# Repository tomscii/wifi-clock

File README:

NTP-sync'd clock with Raspberry Pico W
including SNMP agent serving temperature/humidity sensor values

See: https://tomscii.sig7.se/wifi-clock

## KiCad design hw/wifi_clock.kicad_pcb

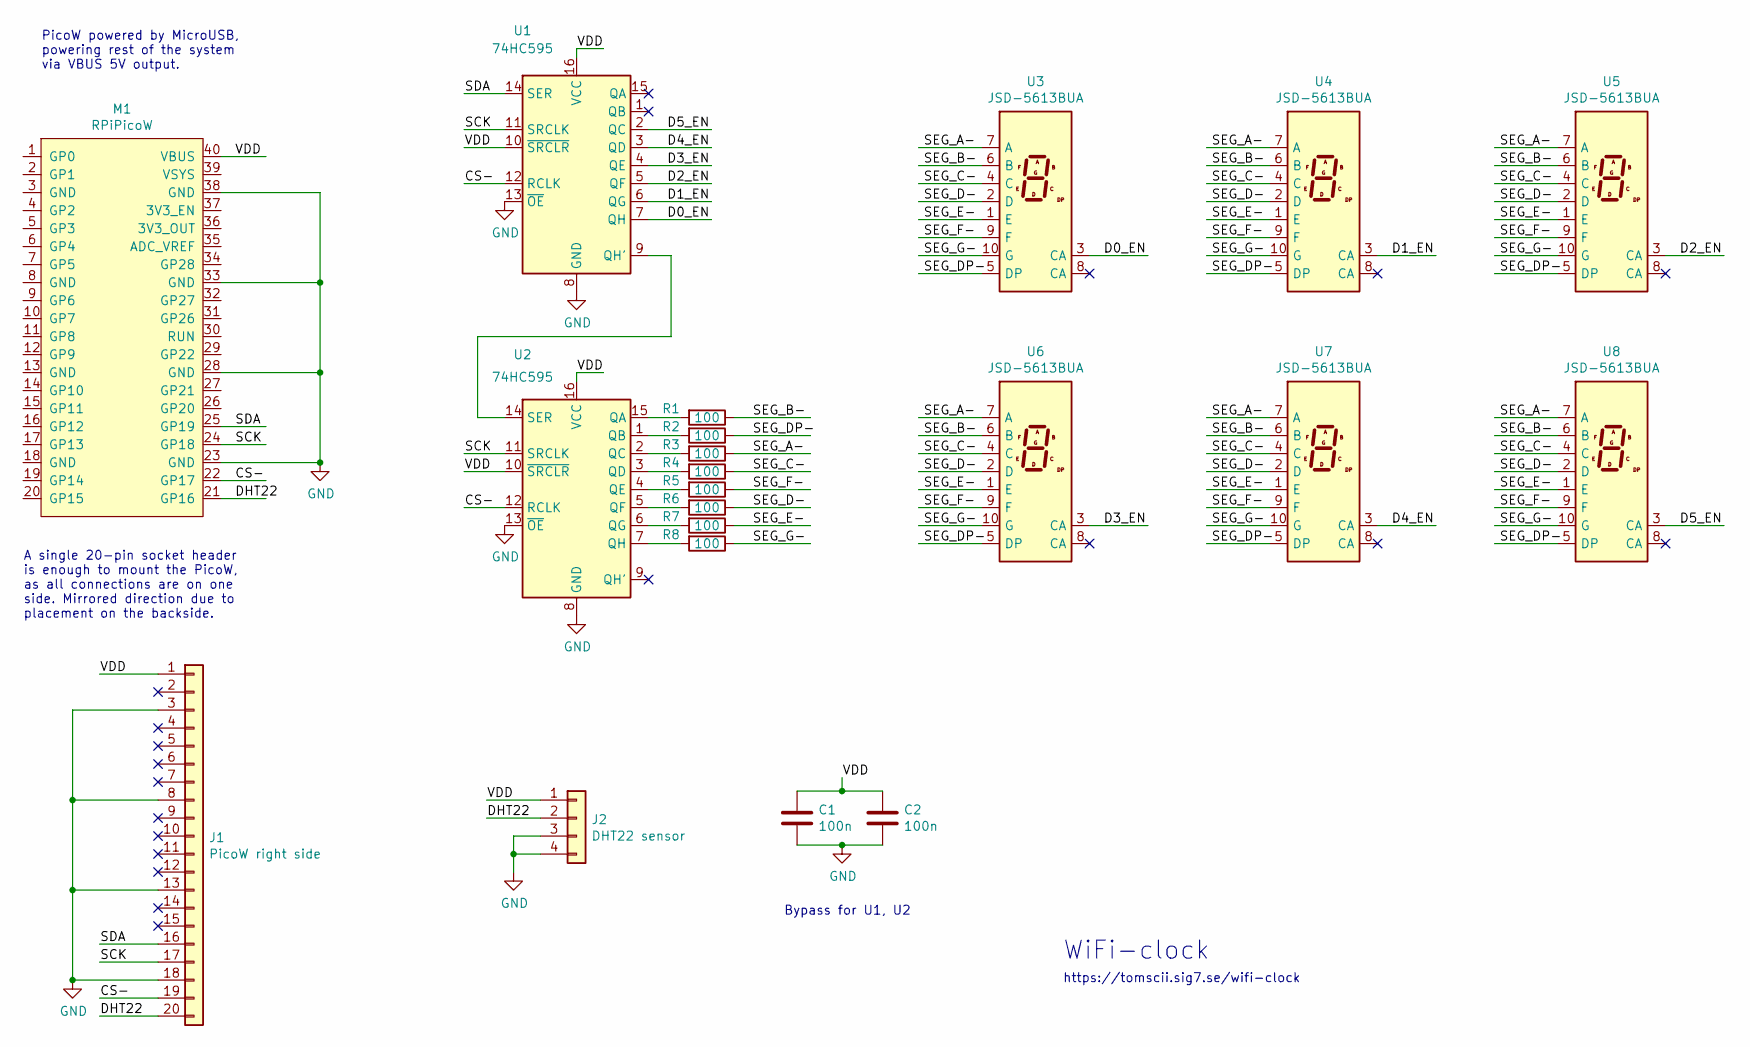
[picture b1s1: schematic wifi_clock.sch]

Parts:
C1, C2: 100n; C_Rect_L7.2mm_W2.5mm_P5.00mm_FKS2_FKP2_MKS2_MKP2
J1: PicoW right side; PinSocket_1x20_P2.54mm_Vertical
J2: DHT22 sensor; PinSocket_1x04_P2.54mm_Vertical
M1: RPiPicoW
R1, R2, R3, R4, R5, R6, R7, R8: 100; R_Axial_DIN0204_L3.6mm_D1.6mm_P7.62mm_Horizontal
U1, U2: 74HC595; DIP-16_W7.62mm
U3, U4, U5, U6, U7, U8: JSD-5613BUA; 7SegmentLED_LTS6760_LTS6780

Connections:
/CS-: J1.19, M1.22 (GP17), U1.12 (RCLK), U2.12 (RCLK)
/D0_EN: U1.7 (QH), U3.3 (CA)
/D1_EN: U1.6 (QG), U4.3 (CA)
/D2_EN: U1.5 (QF), U5.3 (CA)
/D3_EN: U1.4 (QE), U6.3 (CA)
/D4_EN: U1.3 (QD), U7.3 (CA)
/D5_EN: U1.2 (QC), U8.3 (CA)
/DHT22: J1.20, J2.2, M1.21 (GP16)
/SCK: J1.17, M1.24 (GP18), U1.11 (SRCLK), U2.11 (SRCLK)
/SDA: J1.16, M1.25 (GP19), U1.14 (SER)
/SEG_A-: R3.1, U3.7 (A), U4.7 (A), U5.7 (A), U6.7 (A), U7.7 (A), U8.7 (A)
/SEG_B-: R1.1, U3.6 (B), U4.6 (B), U5.6 (B), U6.6 (B), U7.6 (B), U8.6 (B)
/SEG_C-: R4.1, U3.4 (C), U4.4 (C), U5.4 (C), U6.4 (C), U7.4 (C), U8.4 (C)
/SEG_D-: R6.1, U3.2 (D), U4.2 (D), U5.2 (D), U6.2 (D), U7.2 (D), U8.2 (D)
/SEG_DP-: R2.1, U3.5 (DP), U4.5 (DP), U5.5 (DP), U6.5 (DP), U7.5 (DP), U8.5 (DP)
/SEG_E-: R7.1, U3.1 (E), U4.1 (E), U5.1 (E), U6.1 (E), U7.1 (E), U8.1 (E)
/SEG_F-: R5.1, U3.9 (F), U4.9 (F), U5.9 (F), U6.9 (F), U7.9 (F), U8.9 (F)
/SEG_G-: R8.1, U3.10 (G), U4.10 (G), U5.10 (G), U6.10 (G), U7.10 (G), U8.10 (G)
/VDD: C1.1, C2.1, J1.1, J2.1, M1.40 (VBUS), U1.10 (~SRCLR), U1.16 (VCC), U2.10 (~SRCLR), U2.16 (VCC)
GND: C1.2, C2.2, J1.3, J1.8, J1.13, J1.18, J2.3, J2.4, M1.23 (GND), M1.28 (GND), M1.33 (GND), M1.38 (GND), U1.8 (GND), U1.13 (~OE), U2.8 (GND), U2.13 (~OE)
unnamed: R1.2, U2.15 (QA)
unnamed: R2.2, U2.1 (QB)
unnamed: R3.2, U2.2 (QC)
unnamed: R4.2, U2.3 (QD)
unnamed: R5.2, U2.4 (QE)
unnamed: R6.2, U2.5 (QF)
unnamed: R7.2, U2.6 (QG)
unnamed: R8.2, U2.7 (QH)
unnamed: U1.9 (QH'), U2.14 (SER)

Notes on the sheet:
PicoW powered by MicroUSB, powering rest of the system via VBUS 5V output.
A single 20-pin socket header is enough to mount the PicoW, as all connections are on one side. Mirrored direction due to placement on the backside.
WiFi-clock
https://tomscii.sig7.se/wifi-clock
Bypass for U1, U2

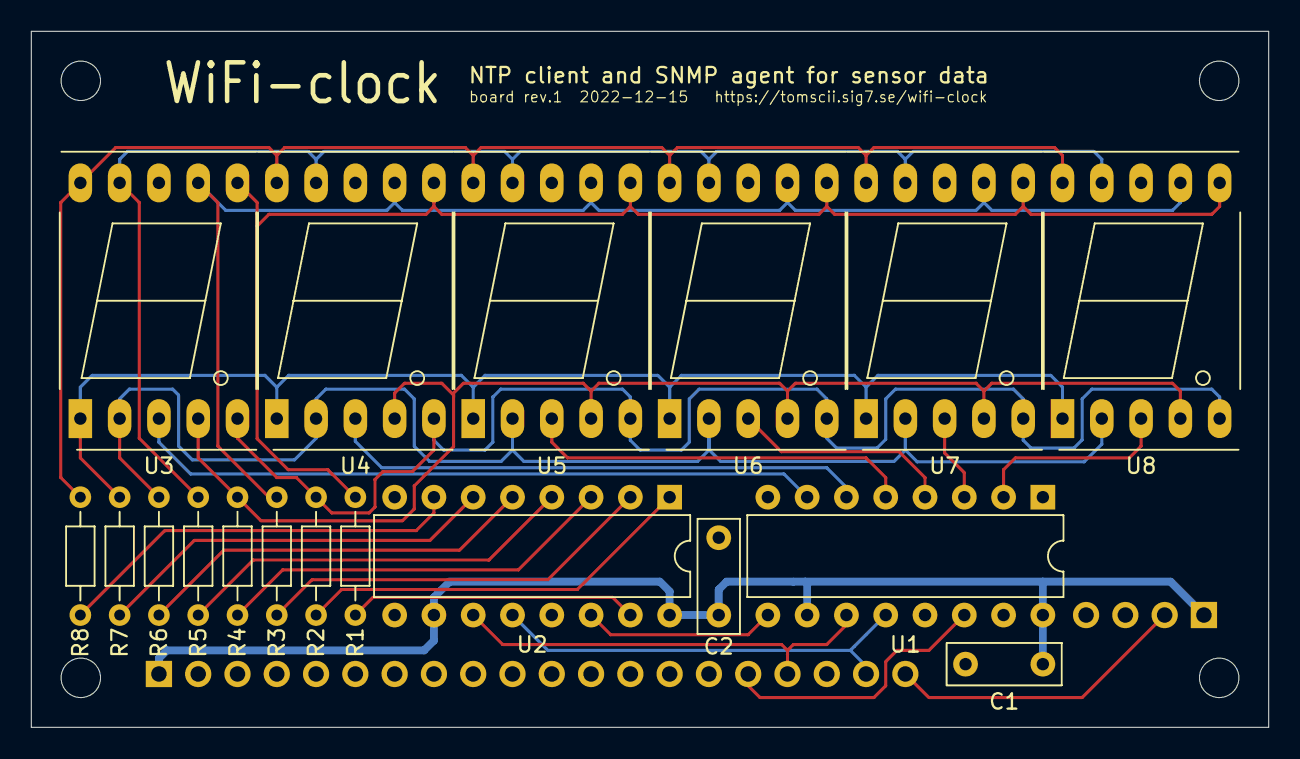
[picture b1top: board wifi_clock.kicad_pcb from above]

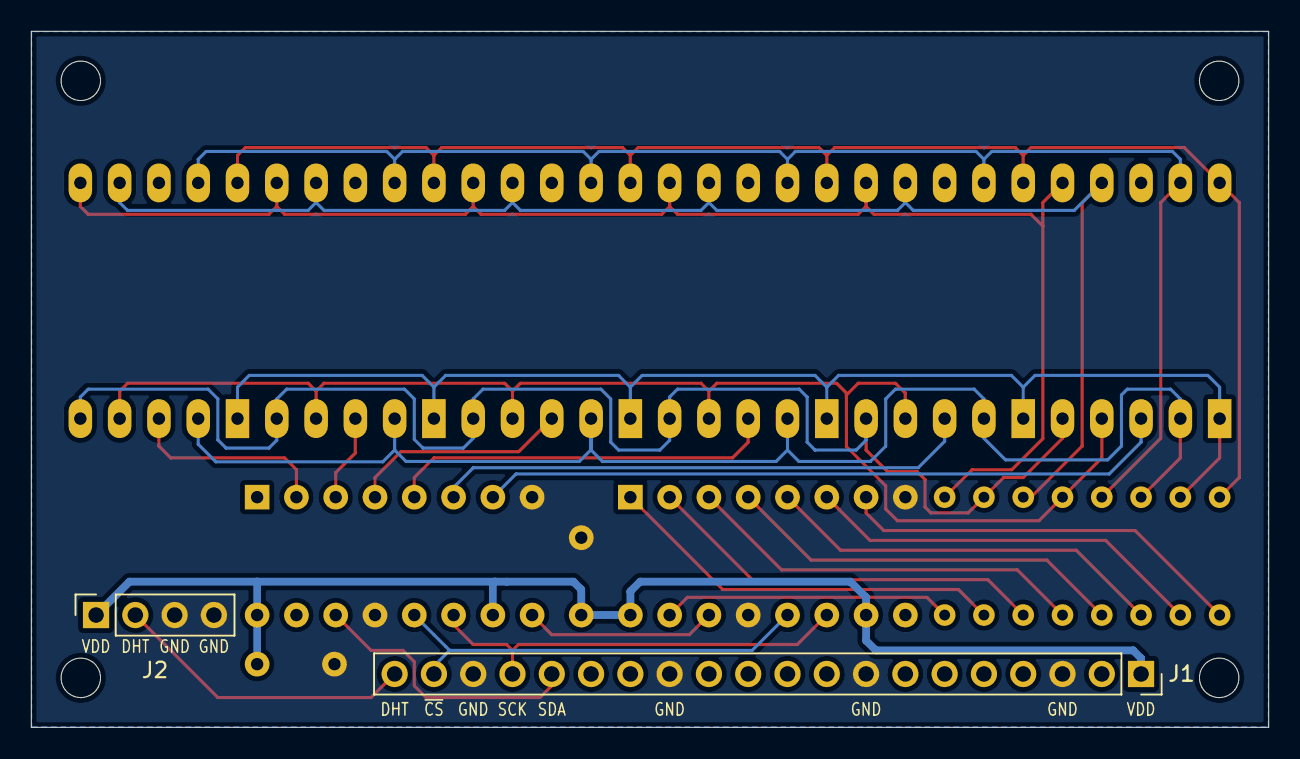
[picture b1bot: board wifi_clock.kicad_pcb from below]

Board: 2 copper layers, 80.0 x 45.0 mm, 20 parts (2 on the bottom side), 29 nets.

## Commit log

2022-10-30 Initial commit (initial HW design, SW PoC)
2022-11-06 Use the RTC clock and display accurate time
2022-11-08 Add network resilience (reconnect logic); receive SNMP packets
2022-11-09 Separate code into modules
2022-11-10 A primitive SNMP agent
2022-11-11 Allow SNMP request id between 0 and 4 bytes
2022-11-11 Serve the Entity-sensor-MIB with temperature and humidity values
2022-12-15 First prototype PCB sent to AISLER manufacturing on 2022-12-15
2022-12-29 Fix digits ordering (final version built as prototype)
2023-02-25 Implement DST auto-adjustment
2023-03-05 DHT: Fix conv of neg temps; adjust bit threshold; print raw data on failed reads
2023-03-05 Control (reduce) the display brightness based on time of day
2023-04-02 Last changes before publication
2024-01-10 Migration notice
